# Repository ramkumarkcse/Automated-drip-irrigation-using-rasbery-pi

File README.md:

# Automated-drip-irrigation-using-rasbery-pi
Introduction 

It is an automated system designed to take good care of your plants while you travel for a long time.The propose is to keep track of humidity levels and once in a while drip some water in your plants if they feel thirst. 

How the system works 

The concept is very simple, the system is composed by the following hardware:      

Arduino (I use the pro mini since it's tiny and you can weld according to your needs)      
Raspberry Pi as an interface to arduino (read sensors, upload new hex files if needed)      
Sensors      
Tiny pump      
Bucket with water      
Gardena micro dipping system      
Android phone to check the status of your plants 

The whole system is controlled by the arduino microcontroller. It checks the humidity sensors every cycle and sets a variable to true or false in case the sole conditions and amount of water on it. If it's dryi, according to a predefined threshold, it will drip water for few seconds or until the sole turns to hidratate enough.

How to use it

Import the Arduino file into an arduino IDE     
Import the android project to your IDE (I use eclipse)     
Copy the bridge file tcp_server.py into your raspberry Pi and set it up under your /etc/rc.local by adding the following line: (sleep 10;python /path/where/you/copied/tcp_server.py)&amp;

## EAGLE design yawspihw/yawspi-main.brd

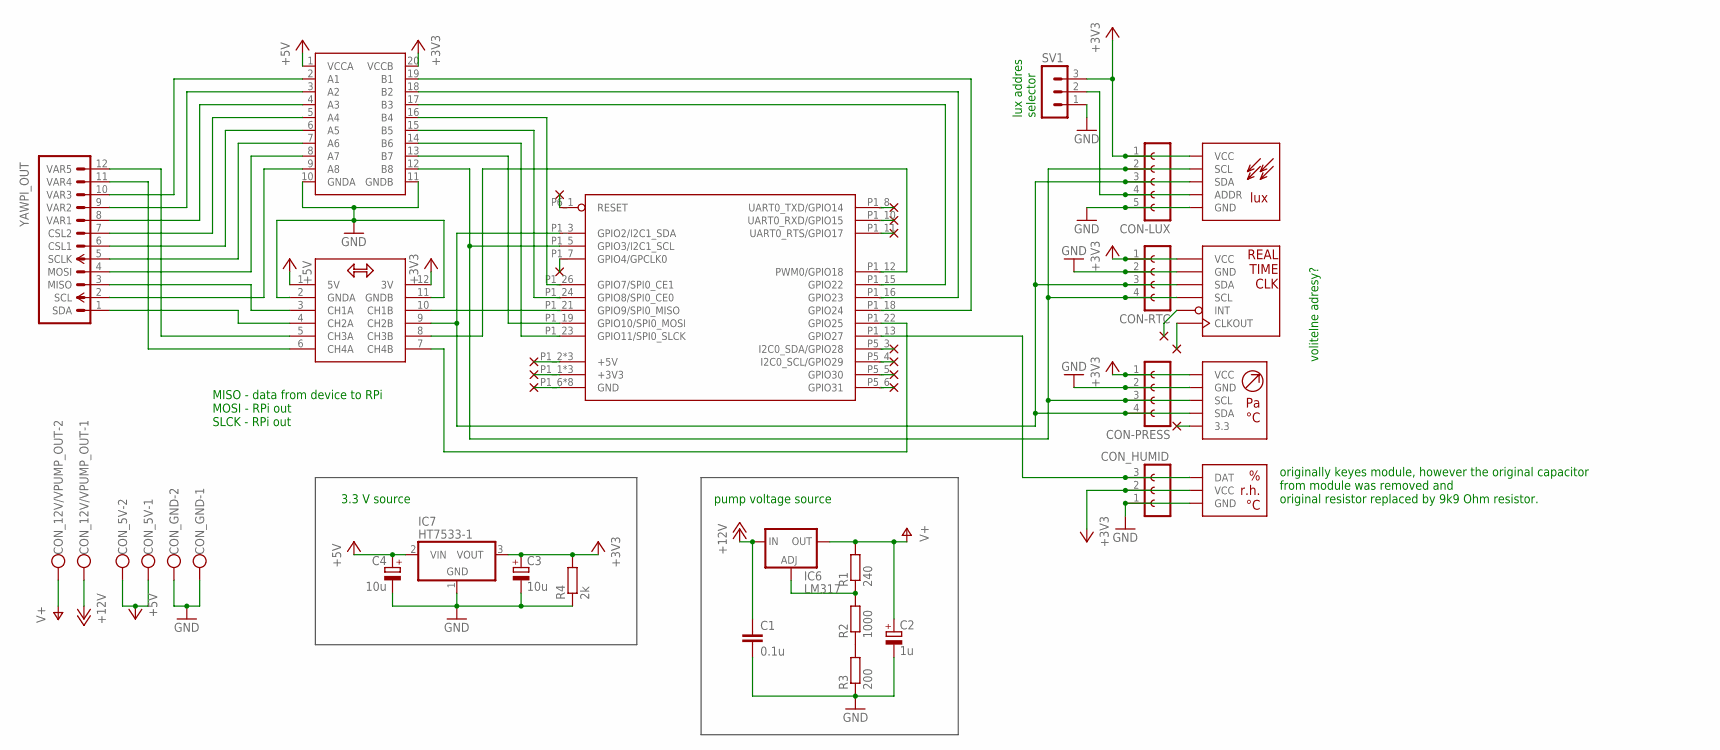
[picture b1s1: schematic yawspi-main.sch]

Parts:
C1: 0.1u; C025-025X050
C2: 1u; E2,5-6E
C3, C4: 10u; E2,5-5
CON-LUX: FE05-1
CON-PRESS: FE04-1
CON-RTC: FE04-1
CON_5V, CON_12V/VPUMP_OUT: W237-102
CON_GND: W237-102
CON_HUMID: FE03-1
IC6: LM317; 317TS
IC7: HT7533-1; TO92
R1: 240; 0204V
R2: 1000; 0204V
R3: 200; 0204V
R4: 2k; 0204V
SV1: MA03-1
U$1: RPI-B-V2HOLES; RPI-B-V2-HOLES
U$2: BIDIR_CONVERSION_MODULE
U$3: LEVEL_CONVERSION_MODULE
YAWPI_OUT: CON-YAWPI-OUT; MA12-1

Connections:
+3V3: C3.+, CON-LUX.1, CON-PRESS.1, CON-RTC.1, CON_HUMID.2, IC7.3 (VOUT), R4.2, SV1.3, U$2.12 (3V), U$3.20 (VCCB)
+5V: C4.+, CON_5V.1, CON_5V.2, IC7.2 (VIN), U$2.1 (5V), U$3.1 (VCCA)
+12V: C1.1, CON_12V/VPUMP_OUT.1, IC6.3 (IN)
GND: C1.2, C2.-, C3.-, C4.-, CON-LUX.5, CON-PRESS.2, CON-RTC.2, CON_GND.1, CON_GND.2, CON_HUMID.1, IC7.1 (GND), R3.1, R4.1, SV1.1, U$2.2 (GNDA), U$2.11 (GNDB), U$3.10 (GNDA), U$3.11 (GNDB)
MOSI: U$1.P1_19 (GPIO10/SPI0_MOSI), U$3.13 (B7)
unnamed: U$3.9 (A8), YAWPI_OUT.2 (SCL)
unnamed: U$3.6 (A5), YAWPI_OUT.6 (CSL1)
unnamed: U$2.4 (CH2A), YAWPI_OUT.1 (SDA)
unnamed: U$1.P1_21 (GPIO9/SPI0_MISO), U$2.10 (CH1B)
unnamed: U$3.7 (A6), YAWPI_OUT.5 (SCLK)
unnamed: U$3.8 (A7), YAWPI_OUT.4 (MOSI)
unnamed: U$2.3 (CH1A), YAWPI_OUT.3 (MISO)
unnamed: U$3.5 (A4), YAWPI_OUT.7 (CSL2)
unnamed: U$1.P1_12 (PWM0/GPIO18), U$2.8 (CH3B)
unnamed: U$1.P1_22 (GPIO25), U$2.7 (CH4B)
unnamed: U$3.4 (A3), YAWPI_OUT.8 (VAR1)
unnamed: U$3.3 (A2), YAWPI_OUT.9 (VAR2)
unnamed: U$3.2 (A1), YAWPI_OUT.10 (VAR3)
unnamed: U$2.6 (CH4A), YAWPI_OUT.11 (VAR4)
unnamed: U$2.5 (CH3A), YAWPI_OUT.12 (VAR5)
unnamed: U$1.P1_24 (GPIO8/SPI0_CE0), U$3.15 (B5)
unnamed: U$1.P1_26 (GPIO7/SPI0_CE1), U$3.16 (B4)
unnamed: U$1.P1_15 (GPIO22), U$3.17 (B3)
unnamed: U$1.P1_16 (GPIO23), U$3.18 (B2)
unnamed: U$1.P1_18 (GPIO24), U$3.19 (B1)
unnamed: CON_HUMID.3, U$1.P1_13 (GPIO27)
unnamed: U$1.P1_6 (GND), U$1.P1_9 (GND), U$1.P1_14 (GND), U$1.P1_20 (GND), U$1.P1_25 (GND), U$1.P5_7 (GND), U$1.P5_8 (GND), U$1.P6_2 (GND)
unnamed: CON-LUX.4, SV1.2
unnamed: U$1.P1_2 (+5V), U$1.P1_4 (+5V), U$1.P5_1 (+5V)
unnamed: U$1.P1_1 (+3V3), U$1.P1_17 (+3V3), U$1.P5_2 (+3V3)
unnamed: IC6.1 (ADJ), R1.1, R2.2
unnamed: R2.1, R3.2
SCL: CON-LUX.2, CON-PRESS.3, CON-RTC.4, U$1.P1_5 (GPIO3/I2C1_SCL), U$3.12 (B8)
SDA: CON-LUX.3, CON-PRESS.4, CON-RTC.3, U$1.P1_3 (GPIO2/I2C1_SDA), U$2.9 (CH2B)
SLCK: U$1.P1_23 (GPIO11/SPI0_SLCK), U$3.14 (B6)
V+: C2.+, CON_12V/VPUMP_OUT.2, IC6.2 (OUT), R1.2

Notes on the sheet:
3.3 V source
MISO - data from device to RPi MOSI - RPi out SLCK - RPi out
pump voltage source
volitelne adresy?
lux addres selector
originally keyes module, however the original capacitor from module was removed and original resistor replaced by 9k9 Ohm resistor.

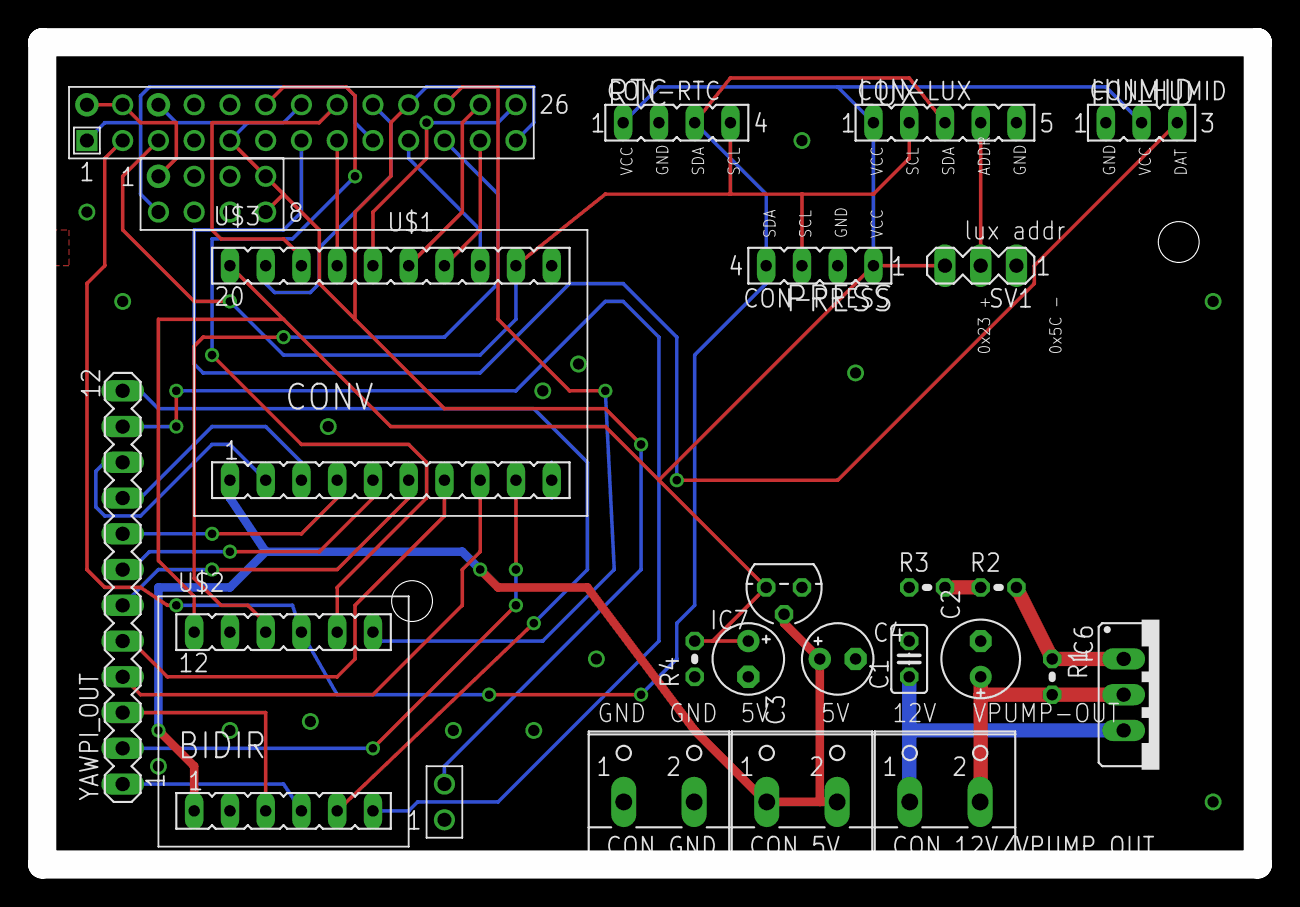
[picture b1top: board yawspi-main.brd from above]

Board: 2 copper layers, 86.4 x 58.4 mm, 22 parts (0 on the bottom side), 36 nets.

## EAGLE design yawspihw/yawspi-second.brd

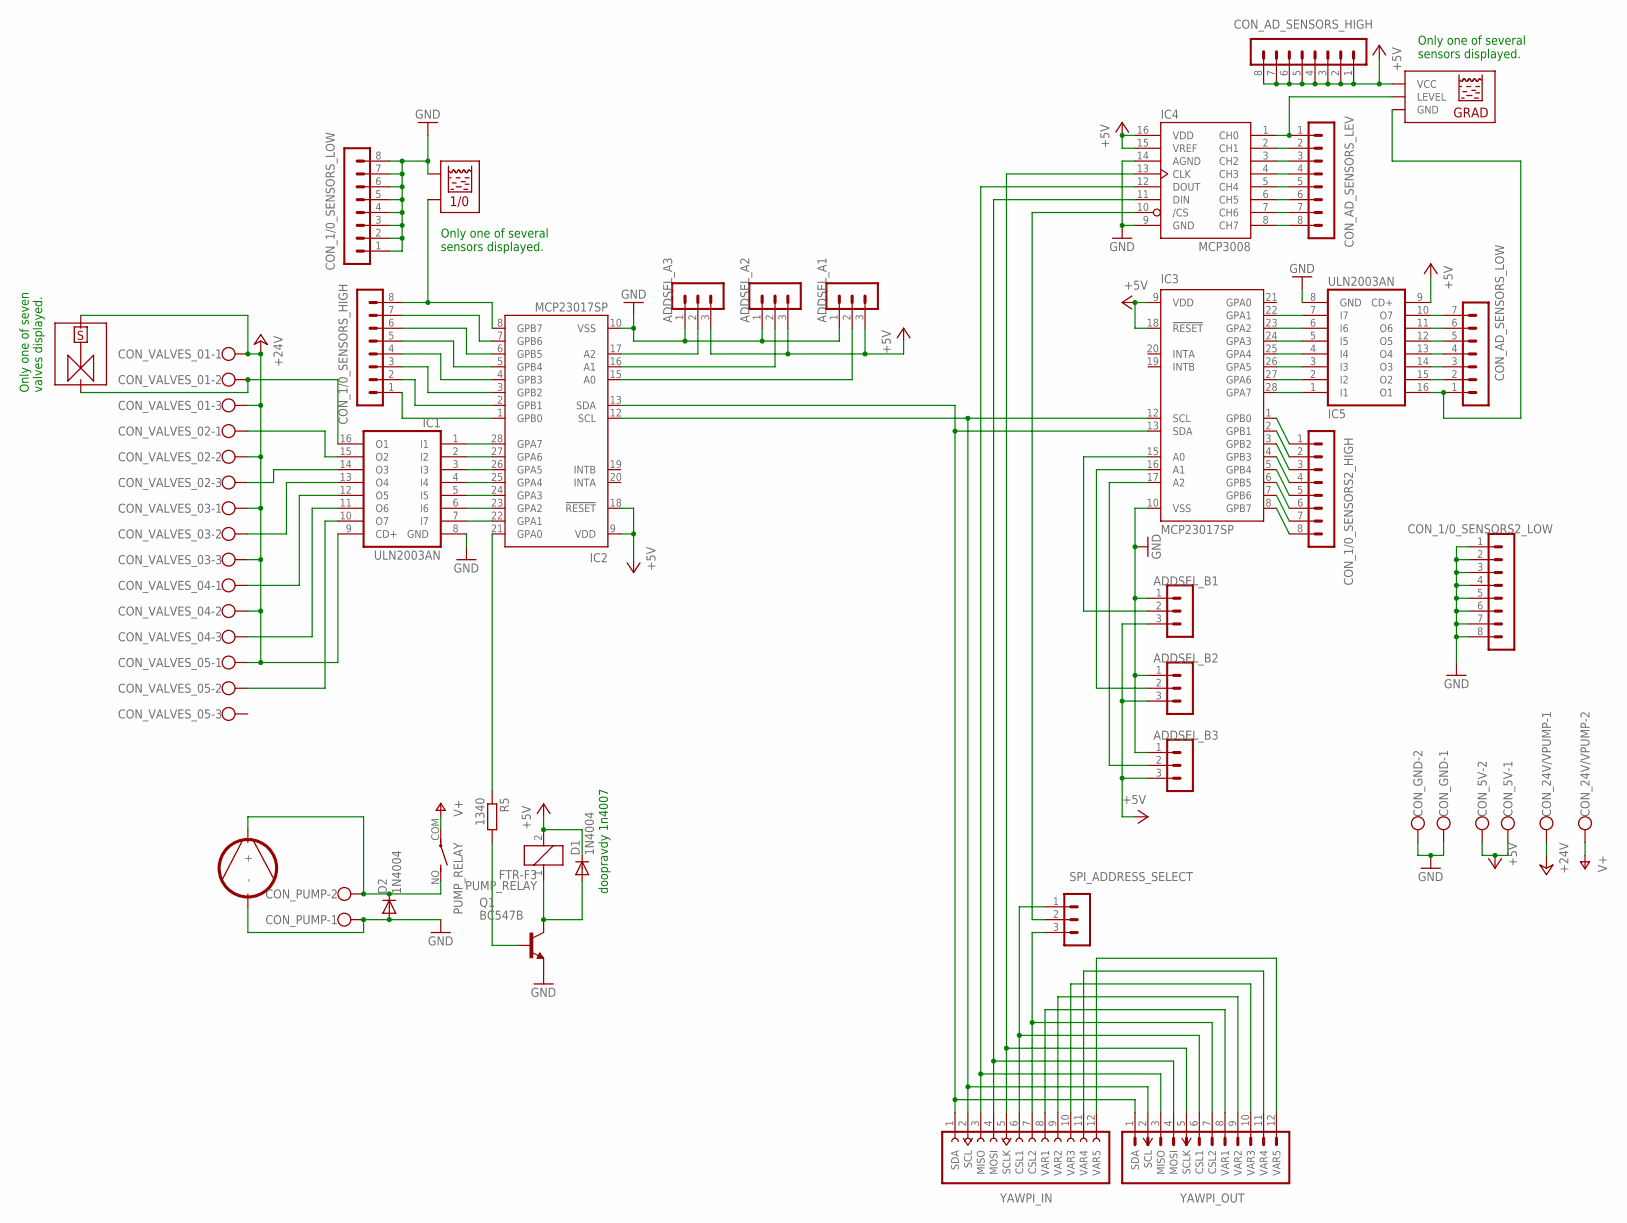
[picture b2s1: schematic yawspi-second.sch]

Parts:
ADDSEL_A1, ADDSEL_A2, ADDSEL_A3: MA03-1
ADDSEL_B1, ADDSEL_B2, ADDSEL_B3: MA03-1
CON_1/0_SENSORS2_HIGH, CON_1/0_SENSORS2_LOW, CON_1/0_SENSORS_HIGH, CON_1/0_SENSORS_LOW: MA08-1_SHORTPAD
CON_5V, CON_24V/VPUMP: W237-102
CON_AD_SENSORS_HIGH: MA08-1_SHORTPAD
CON_AD_SENSORS_LEV: MA08-1_SHORTPAD
CON_AD_SENSORS_LOW: MA07-1_SHORTPAD
CON_GND: W237-102
CON_PUMP: W237-102
CON_VALVES_01, CON_VALVES_02, CON_VALVES_03, CON_VALVES_04, CON_VALVES_05: W237-102-SMALL
D1, D2: 1N4004; DO41-10
IC1, IC5: ULN2003AN; DIL16
IC2, IC3: MCP23017SP; DIL28-3
IC4: MCP3008; DIL16
PUMP_RELAY: FTR-F3; FTR-F3_PACKAGE
Q1: BC547B; TO92
R5: 1340; 0204/7
SPI_ADDRESS_SELECT: MA03-1
YAWPI_IN: CON-YAWPI-IN; FE12
YAWPI_OUT: CON-YAWPI-OUT; MA12-1

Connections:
+5V: ADDSEL_A1.3, ADDSEL_A2.3, ADDSEL_A3.3, ADDSEL_B1.3, ADDSEL_B2.3, ADDSEL_B3.3, CON_5V.1, CON_5V.2, CON_AD_SENSORS_HIGH.1, CON_AD_SENSORS_HIGH.2, CON_AD_SENSORS_HIGH.3, CON_AD_SENSORS_HIGH.4, CON_AD_SENSORS_HIGH.5, CON_AD_SENSORS_HIGH.6, CON_AD_SENSORS_HIGH.7, CON_AD_SENSORS_HIGH.8, D1.C, IC2.9 (VDD), IC2.18 (!RESET), IC3.9 (VDD), IC3.18 (!RESET), IC4.15 (VREF), IC4.16 (VDD), IC5.9 (CD+), PUMP_RELAY.2
+24V: CON_24V/VPUMP.1, CON_VALVES_01.1, CON_VALVES_01.3, CON_VALVES_02.2, CON_VALVES_03.1, CON_VALVES_03.3, CON_VALVES_04.2, CON_VALVES_05.1, IC1.9 (CD+)
GND: ADDSEL_A1.1, ADDSEL_A2.1, ADDSEL_A3.1, ADDSEL_B1.1, ADDSEL_B2.1, ADDSEL_B3.1, CON_1/0_SENSORS2_LOW.1, CON_1/0_SENSORS2_LOW.2, CON_1/0_SENSORS2_LOW.3, CON_1/0_SENSORS2_LOW.4, CON_1/0_SENSORS2_LOW.5, CON_1/0_SENSORS2_LOW.6, CON_1/0_SENSORS2_LOW.7, CON_1/0_SENSORS2_LOW.8, CON_1/0_SENSORS_LOW.1, CON_1/0_SENSORS_LOW.2, CON_1/0_SENSORS_LOW.3, CON_1/0_SENSORS_LOW.4, CON_1/0_SENSORS_LOW.5, CON_1/0_SENSORS_LOW.6, CON_1/0_SENSORS_LOW.7, CON_1/0_SENSORS_LOW.8, CON_GND.1, CON_GND.2, CON_PUMP.1, D2.A, IC1.8 (GND), IC2.10 (VSS), IC3.10 (VSS), IC4.9 (GND), IC4.14 (AGND), IC5.8 (GND), Q1.1 (E)
unnamed: D1.A, PUMP_RELAY.1, Q1.3 (C)
unnamed: IC3.28 (GPA7), IC5.1 (I1)
unnamed: IC1.7 (I7), IC2.22 (GPA1)
unnamed: IC1.6 (I6), IC2.23 (GPA2)
unnamed: IC1.5 (I5), IC2.24 (GPA3)
unnamed: IC1.4 (I4), IC2.25 (GPA4)
unnamed: IC1.3 (I3), IC2.26 (GPA5)
unnamed: IC1.2 (I2), IC2.27 (GPA6)
unnamed: IC1.1 (I1), IC2.28 (GPA7)
unnamed: IC4.12 (DOUT), YAWPI_IN.3 (MISO), YAWPI_OUT.3 (MISO)
unnamed: IC2.13 (SDA), IC3.13 (SDA), YAWPI_IN.1 (SDA), YAWPI_OUT.1 (SDA)
unnamed: CON_VALVES_01.2, IC1.16 (O1)
unnamed: IC2.12 (SCL), IC3.12 (SCL), YAWPI_IN.2 (SCL), YAWPI_OUT.2 (SCL)
unnamed: IC3.27 (GPA6), IC5.2 (I2)
unnamed: CON_AD_SENSORS_LEV.1, IC4.1 (CH0)
unnamed: CON_VALVES_02.1, IC1.15 (O2)
unnamed: CON_VALVES_05.2, IC1.10 (O7)
unnamed: CON_VALVES_02.3, IC1.14 (O3)
unnamed: CON_VALVES_03.2, IC1.13 (O4)
unnamed: CON_VALVES_04.1, IC1.12 (O5)
unnamed: CON_1/0_SENSORS_HIGH.1, IC2.1 (GPB0)
unnamed: IC3.26 (GPA5), IC5.3 (I3)
unnamed: IC4.11 (DIN), YAWPI_IN.4 (MOSI), YAWPI_OUT.4 (MOSI)
unnamed: CON_VALVES_04.3, IC1.11 (O6)
unnamed: CON_1/0_SENSORS_HIGH.7, IC2.7 (GPB6)
unnamed: CON_1/0_SENSORS_HIGH.6, IC2.6 (GPB5)
unnamed: CON_1/0_SENSORS_HIGH.5, IC2.5 (GPB4)
unnamed: CON_1/0_SENSORS_HIGH.4, IC2.4 (GPB3)
unnamed: CON_1/0_SENSORS_HIGH.3, IC2.3 (GPB2)
unnamed: CON_1/0_SENSORS_HIGH.2, IC2.2 (GPB1)
unnamed: IC3.25 (GPA4), IC5.4 (I4)
unnamed: IC3.24 (GPA3), IC5.5 (I5)
unnamed: CON_AD_SENSORS_LEV.2, IC4.2 (CH1)
unnamed: CON_AD_SENSORS_LEV.3, IC4.3 (CH2)
unnamed: CON_AD_SENSORS_LEV.4, IC4.4 (CH3)
unnamed: CON_AD_SENSORS_LEV.5, IC4.5 (CH4)
unnamed: CON_AD_SENSORS_LEV.6, IC4.6 (CH5)
unnamed: CON_AD_SENSORS_LEV.7, IC4.7 (CH6)
unnamed: CON_AD_SENSORS_LEV.8, IC4.8 (CH7)
unnamed: IC3.23 (GPA2), IC5.6 (I6)
unnamed: IC3.22 (GPA1), IC5.7 (I7)
unnamed: CON_1/0_SENSORS2_HIGH.8, IC3.8 (GPB7)
unnamed: CON_1/0_SENSORS2_HIGH.7, IC3.7 (GPB6)
unnamed: CON_1/0_SENSORS2_HIGH.6, IC3.6 (GPB5)
unnamed: CON_1/0_SENSORS2_HIGH.5, IC3.5 (GPB4)
unnamed: CON_1/0_SENSORS2_HIGH.4, IC3.4 (GPB3)
unnamed: CON_1/0_SENSORS2_HIGH.3, IC3.3 (GPB2)
unnamed: CON_1/0_SENSORS2_HIGH.2, IC3.2 (GPB1)
unnamed: CON_1/0_SENSORS2_HIGH.1, IC3.1 (GPB0)
unnamed: IC4.10 (/CS), SPI_ADDRESS_SELECT.2
unnamed: IC4.13 (CLK), YAWPI_IN.5 (SCLK), YAWPI_OUT.5 (SCLK)
unnamed: CON_AD_SENSORS_LOW.2, IC5.15 (O2)
unnamed: CON_AD_SENSORS_LOW.3, IC5.14 (O3)
unnamed: CON_AD_SENSORS_LOW.4, IC5.13 (O4)
unnamed: CON_AD_SENSORS_LOW.5, IC5.12 (O5)
unnamed: CON_AD_SENSORS_LOW.6, IC5.11 (O6)
unnamed: CON_AD_SENSORS_LOW.7, IC5.10 (O7)
unnamed: Q1.2 (B), R5.2
unnamed: ADDSEL_A3.2, IC2.17 (A2)
unnamed: SPI_ADDRESS_SELECT.3, YAWPI_IN.7 (CSL2), YAWPI_OUT.7 (CSL2)
unnamed: IC2.21 (GPA0), R5.1
unnamed: CON_1/0_SENSORS_HIGH.8, IC2.8 (GPB7)
unnamed: YAWPI_IN.8 (VAR1), YAWPI_OUT.8 (VAR1)
unnamed: YAWPI_IN.9 (VAR2), YAWPI_OUT.9 (VAR2)
unnamed: YAWPI_IN.10 (VAR3), YAWPI_OUT.10 (VAR3)
unnamed: CON_PUMP.2, D2.C, PUMP_RELAY.NO (S)
unnamed: SPI_ADDRESS_SELECT.1, YAWPI_IN.6 (CSL1), YAWPI_OUT.6 (CSL1)
unnamed: ADDSEL_A2.2, IC2.16 (A1)
unnamed: ADDSEL_A1.2, IC2.15 (A0)
unnamed: ADDSEL_B1.2, IC3.15 (A0)
unnamed: ADDSEL_B2.2, IC3.16 (A1)
unnamed: ADDSEL_B3.2, IC3.17 (A2)
unnamed: YAWPI_IN.11 (VAR4), YAWPI_OUT.11 (VAR4)
unnamed: YAWPI_IN.12 (VAR5), YAWPI_OUT.12 (VAR5)
P$2: CON_AD_SENSORS_LOW.1, IC5.16 (O1)
V+: CON_24V/VPUMP.2, PUMP_RELAY.COM

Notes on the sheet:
Only one of seven valves displayed.
Only one of several sensors displayed.
doopravdy 1n4007

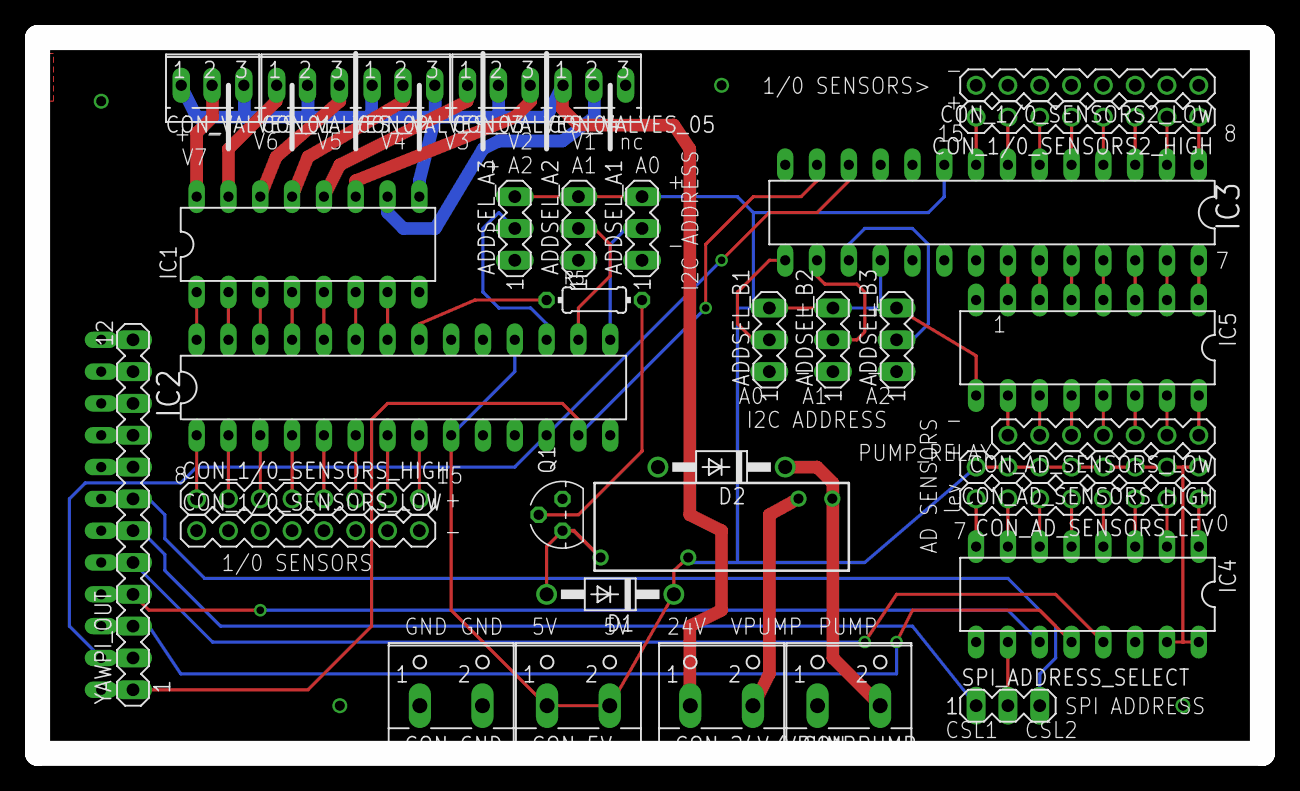
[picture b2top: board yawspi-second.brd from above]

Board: 2 copper layers, 97.8 x 57.1 mm, 35 parts (1 on the bottom side), 79 nets.

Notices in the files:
parts and their libraries:
raspberrypi: This library stands under the CERN Open Hardware Licence.
